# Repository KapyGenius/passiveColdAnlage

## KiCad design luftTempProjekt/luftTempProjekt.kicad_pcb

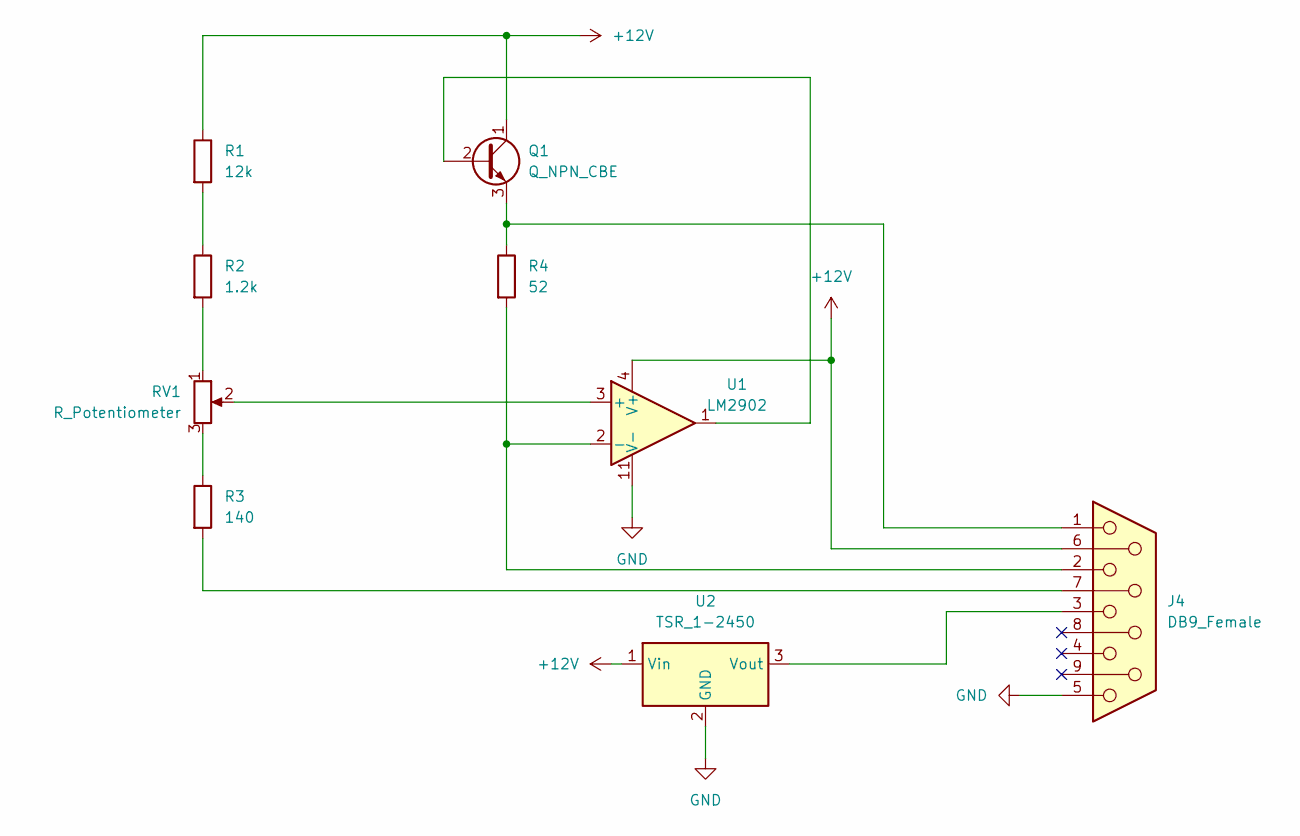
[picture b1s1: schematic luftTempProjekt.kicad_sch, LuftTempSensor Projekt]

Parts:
J4: DB9_Female; DSUB-9_Female_Horizontal_P2.77x2.54mm_EdgePinOffset9.40mm
Q1: Q_NPN_CBE; Potentiometer_ACP_CA6-H2,5_Horizontal
R1: 12k; R_Axial_DIN0204_L3.6mm_D1.6mm_P5.08mm_Horizontal
R2: 1.2k; R_Axial_DIN0204_L3.6mm_D1.6mm_P5.08mm_Horizontal
R3: 140; R_Axial_DIN0204_L3.6mm_D1.6mm_P5.08mm_Horizontal
R4: 52; R_Axial_DIN0204_L3.6mm_D1.6mm_P5.08mm_Horizontal
RV1: R_Potentiometer; Potentiometer_ACP_CA6-H2,5_Horizontal
U1: LM2902; SO-14_3.9x8.65mm_P1.27mm
U2: TSR_1-2450; Converter_DCDC_TRACO_TSR-1_THT

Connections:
+12V: J4.6, Q1.1 (C), R1.1, U1.4 (V+), U2.1 (Vin)
GND: J4.5, U1.11 (V-), U2.2 (GND)
unnamed: J4.1, Q1.3 (E), R4.1
unnamed: J4.2, R4.2, U1.2 (-)
unnamed: J4.3, U2.3 (Vout)
unnamed: J4.7, R3.2
unnamed: Q1.2 (B), U1.1
unnamed: R1.2, R2.1
unnamed: R2.2, RV1.1
unnamed: R3.1, RV1.3
unnamed: RV1.2, U1.3 (+)

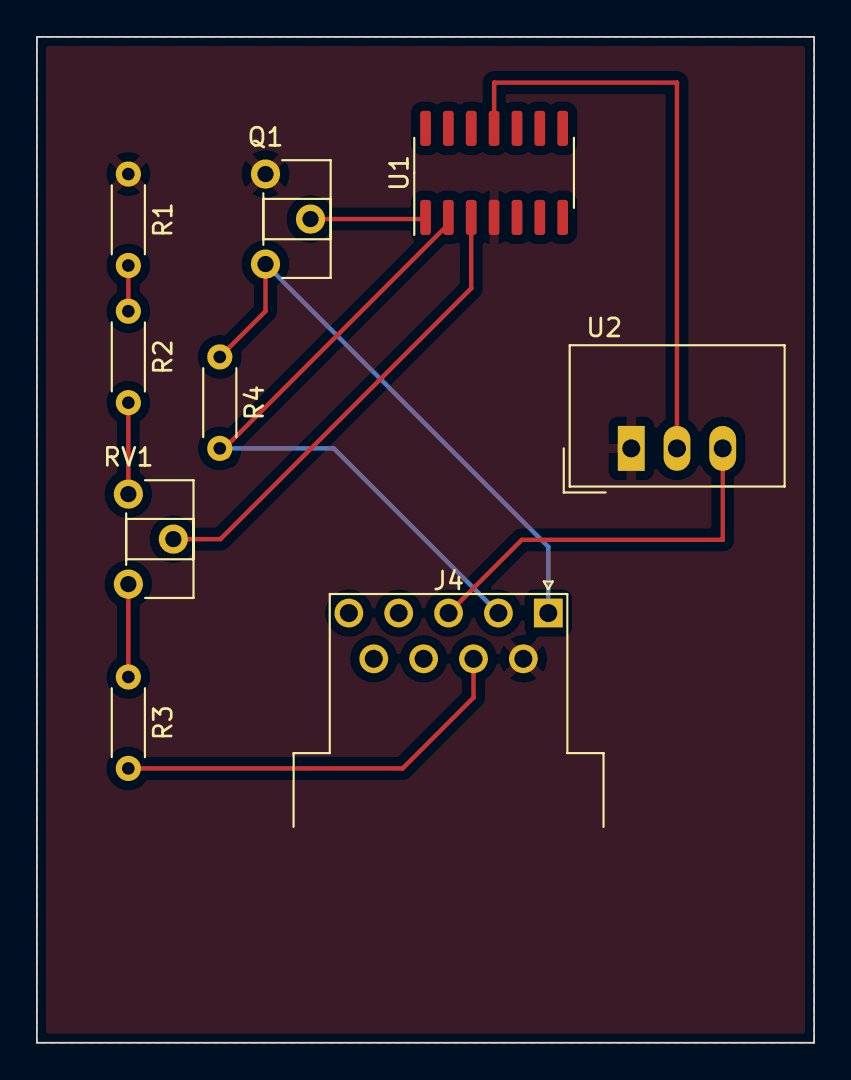
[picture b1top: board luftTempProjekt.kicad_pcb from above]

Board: 2 copper layers, 43.2 x 55.9 mm, 9 parts (0 on the bottom side), 11 nets.

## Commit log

2022-06-27 add export
